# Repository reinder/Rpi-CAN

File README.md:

# Rpi-CAN
Rpi-CAN is a CAN-bus extension board for Raspberry Pi.

The board runs completly on 3.3V and is powered by the Raspberry Pi 3.3 V rail.
Alternativly it can be powered by the Raspberry Pi 5V rail.

The Rpi-CAN uses the [Microchip MCP2515 CAN controller](www.microchip.com/solutionsmcp2515) via SPI.
The MCP2515 is supported by Linux and Raspbian, allthough support for the MCP2515 is missing in the default Raspbian kernel.

**NOTE:** There is no galvanic isolation between the CAN-bus and the Raspberry Pi!

## Components
- R1: Resistor, 0 Ohm, 0805 (Optional: only if directly powered from the 3.3 V rail.)
- R2: Resistor, 120 Ohm, 0805 
- R3: Resistor, 10 kOhm, 0805 
- R4: Resistor, 10 kOhm, 0805 
- R5: Resistor, 0 Ohm, 0805 (Optional: for connecting *optional ground* to the Raspberry Pi ground) 
- R6: Resistor, 0 Ohm, 0805 (Optional: for connecting *CAN-ground* to the Raspberry Pi ground)
- R7: Resistor, 0 Ohm, 0805 (Optional: for connecting *optional power* to the Raspberry Pi 5V rail)
- C1: Ceramic Capacitor, 100 nF, 0805
- C1: Ceramic Capacitor, 100 nF, 0805
- C5: Ceramic Capacitor, 18 pF, 0805
- C6: Ceramic Capacitor, 18 pF, 0805
- C9: Ceramic Capacitor, 100 nF, 0805 (Optional: only if powered from 5 V rail.)
- C10: Ceramic Capacitor, 100 nF, 0805 (Optional: only if powered from 5 V rail.)
- Q1: Crystal, 20 MHz, SM49
- IC1: CAN tranciever, SN65HVD233-HT, SO-8
- IC2: CAN controller, MCP2515, SO-18W
- IC3: Voltage regulator 3.3V, XC6221B332MR, SOT25 (Optional: only if powered from 5 V rail.)
- JP1: 3 pin jumper, RM254
- JP2: 2 pin jumper, RM254
- JP3: 3 pin jumper, RM254
- X2: Pin header 2x13 female, RM254 
- X3: D-sub 9 pin male, solder

## Jumpers
- JP1 is for selecting the SPI chip select (CS0 or CS1).
- JP2 is for enabling/disabling the 120 Ohm bus temination resitor.
- JP3 is for selecting the interrupt GPIO (23 or 24).

## CAN-bus connector pinout
1. Not connected
2. CAN Low
3. CAN ground
4. Not connected
5. Not connected
6. Optional ground
7. CAN High
8. Not connected
9. Optional power

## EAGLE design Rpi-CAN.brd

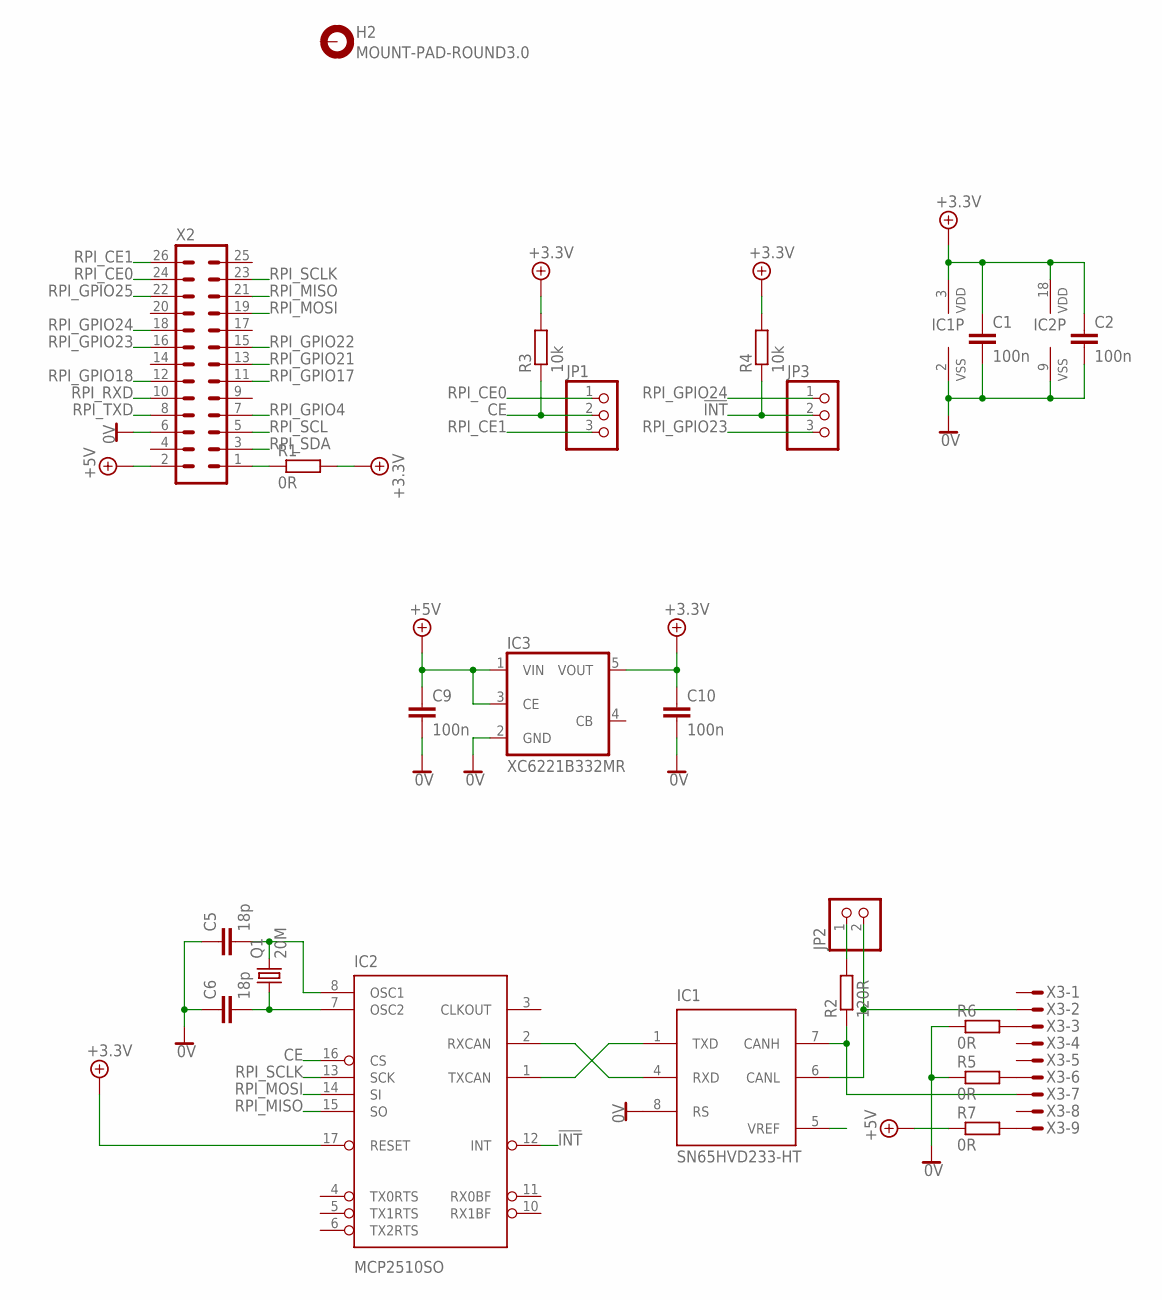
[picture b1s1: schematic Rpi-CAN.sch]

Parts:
C1, C2, C9, C10: 100n; C0805
C5, C6: 18p; C0805
H2: MOUNT-PAD-ROUND3.0; 3,0-PAD
IC1: SN65HVD233-HT; SO-08
IC2: MCP2510SO; SO-18W
IC3: XC6221B332MR; SOT25
JP1, JP3: PINHD-1X3; 1X03
JP2: PINHD-1X2; 1X02
Q1: 20M; SM49
R1, R5, R6, R7: 0R; R0805
R2: 120R; R0805
R3, R4: 10k; R0805
X2: MA13-2
X3: M09DS; M09D

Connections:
0V: C1.2, C2.2, C5.1, C6.1, C9.2, C10.2, IC1.2 (VSS), IC1.8 (RS), IC2.9 (VSS), IC3.2 (GND), R5.1, R6.1, X2.6
!INT: IC2.12 (INT), JP3.2, R4.1
+3.3V: C1.1, C2.1, C10.1, IC1.3 (VDD), IC2.17 (RESET), IC2.18 (VDD), IC3.5 (VOUT), R1.2, R3.2, R4.2
+5V: C9.1, IC3.1 (VIN), IC3.3 (CE), R7.1, X2.2
CE: IC2.16 (CS), JP1.2, R3.1
unnamed: IC1.6 (CANL), JP2.2, X3.2
unnamed: R5.2, X3.6
unnamed: IC1.7 (CANH), R2.1, X3.7
unnamed: R6.2, X3.3
unnamed: R7.2, X3.9
unnamed: IC1.4 (RXD), IC2.2 (RXCAN)
unnamed: IC1.1 (TXD), IC2.1 (TXCAN)
unnamed: C5.2, IC2.8 (OSC1), Q1.2
unnamed: C6.2, IC2.7 (OSC2), Q1.1
unnamed: JP2.1, R2.2
unnamed: R1.1, X2.1
RPI_CE0: JP1.1, X2.24
RPI_CE1: JP1.3, X2.26
RPI_GPIO4: X2.7
RPI_GPIO17: X2.11
RPI_GPIO18: X2.12
RPI_GPIO21: X2.13
RPI_GPIO22: X2.15
RPI_GPIO23: JP3.3, X2.16
RPI_GPIO24: JP3.1, X2.18
RPI_GPIO25: X2.22
RPI_MISO: IC2.15 (SO), X2.21
RPI_MOSI: IC2.14 (SI), X2.19
RPI_RXD: X2.10
RPI_SCL: X2.5
RPI_SCLK: IC2.13 (SCK), X2.23
RPI_SDA: X2.3
RPI_TXD: X2.8

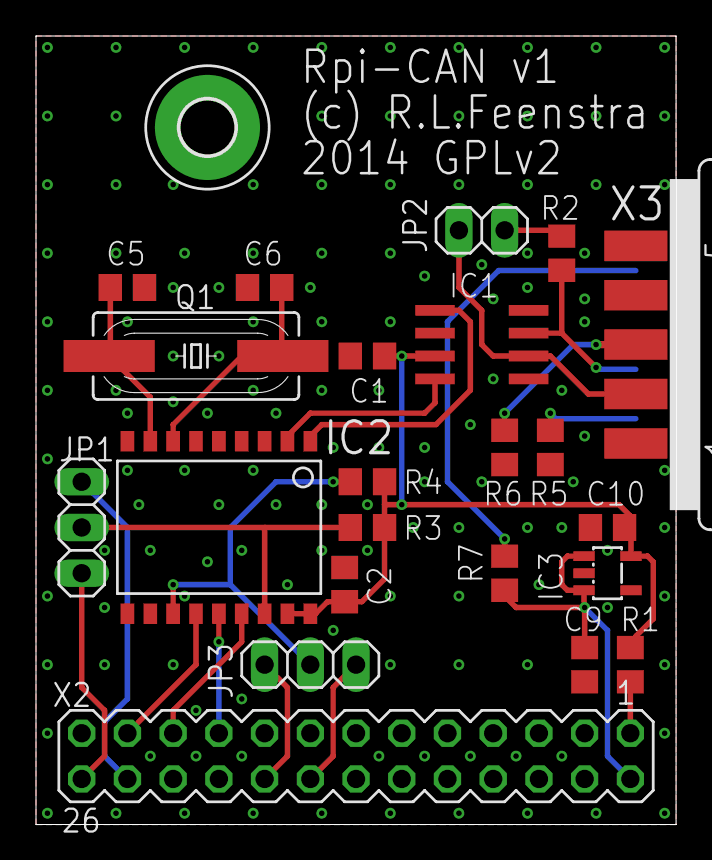
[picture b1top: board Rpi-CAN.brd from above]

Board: 2 copper layers, 35.6 x 43.8 mm, 23 parts (0 on the bottom side), 23 nets.

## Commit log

2015-01-17 Initial commit, as designed and produced in june 2014.
2015-01-20 Swapped JP2 and JP3 description.
2015-01-20 Added resitor for connecting Raspberry Pi 5V rail to CAN optional power.
2015-01-20 Added CAN-bus connector pinout.

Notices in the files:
Rpi-CAN.brd:
2014 GPLv2
